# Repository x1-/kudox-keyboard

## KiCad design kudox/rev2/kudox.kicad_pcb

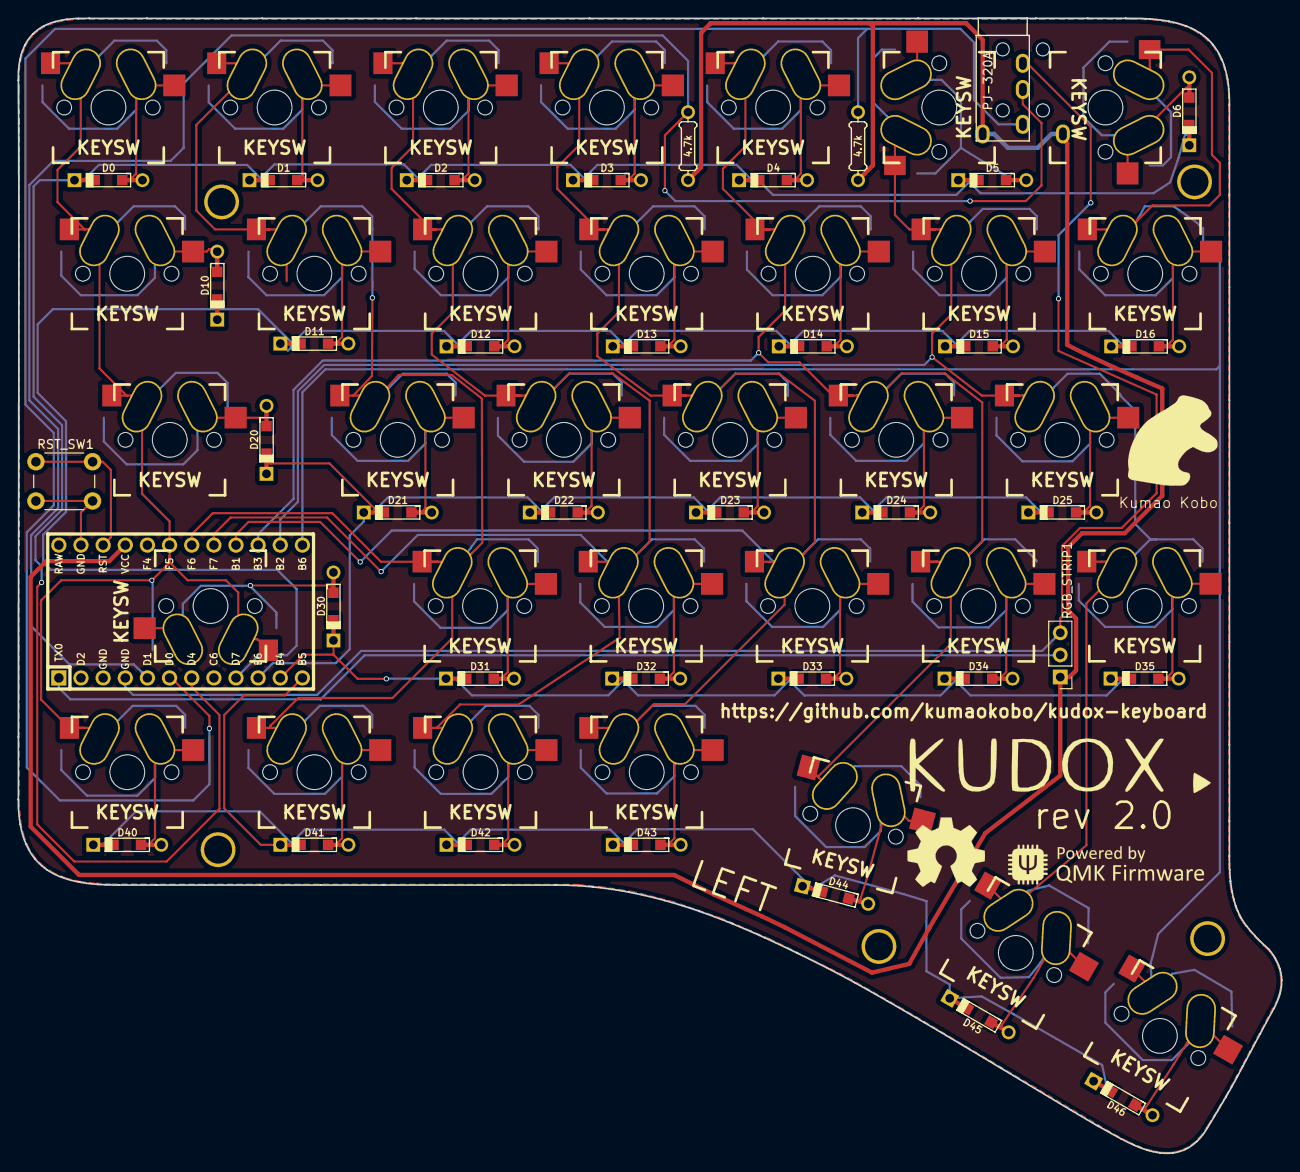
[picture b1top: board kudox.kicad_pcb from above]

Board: 2 copper layers, 144.9 x 130.2 mm, 78 parts (0 on the bottom side), 51 nets.

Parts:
-3: OSHW-Logo2_14.6x12mm_SilkScreen; OSHW-Symbol_8.9x8mm_SilkScreen
D0, D1, D2, D3, D4, D5, D6, D10, D11, D12, D13, D14, D15, D16, D20, D21, D22, D23, D24, D25, D30, D31, D32, D33, D34, D35, D40, D41, D42, D43, D44, D45, D46: D; Diode-dual
HOLE_M3, HOLE_M3#2, HOLE_M3#3, HOLE_M3#4, HOLE_M3#5: VAL**; HOLE_M3
K0, K1, K2, K3, K4, K5, K6, K10, K11, K12, K13, K14, K15, K16, K20, K21, K22, K23, K24, K25, K30, K31, K32, K33, K34, K35, K40, K41, K42, K43, K44, K45, K46: KEYSW; Mx_hotswappable
R1, R2: 4.7k; Resistor-Compact
RGB_STRIP1: Conn_01x03; Pin_Header_Straight_1x03_Pitch2.54mm
RST_SW1: SW_PUSH; SW_PUSH_6mm_h4.3mm
TRRS1: Audio-Jack-4; TRRS-PJ-320A-dual
U1: ProMicro; ArduinoProMicro

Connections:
GND: RGB_STRIP1.3, RST_SW1.2, TRRS1.4, U1.3, U1.4, U1.23
unnamed: D0.2, K0.2
unnamed: D1.2, K1.2
unnamed: D2.2, K2.2
unnamed: D3.2, K3.2
unnamed: D4.2, K4.2
unnamed: D5.2, K5.2
unnamed: D6.2, K6.2
unnamed: D10.2, K10.2
unnamed: D11.2, K11.2
unnamed: D12.2, K12.2
unnamed: D13.2, K13.2
unnamed: D14.2, K14.2
unnamed: D15.2, K15.2
unnamed: D16.2, K16.2
unnamed: D20.2, K20.2
unnamed: D21.2, K21.2
unnamed: D22.2, K22.2
unnamed: D23.2, K23.2
unnamed: D24.2, K24.2
unnamed: D25.2, K25.2
unnamed: D30.2, K30.2
unnamed: D31.2, K31.2
unnamed: D32.2, K32.2
unnamed: D33.2, K33.2
unnamed: D34.2, K34.2
unnamed: D35.2, K35.2
unnamed: D40.2, K40.2
unnamed: D41.2, K41.2
unnamed: D42.2, K42.2
unnamed: D43.2, K43.2
unnamed: D44.2, K44.2
unnamed: D45.2, K45.2
unnamed: D46.2, K46.2
RST: RST_SW1.1, U1.22
SCL: R2.1, TRRS1.2, U1.6
SDA: R1.1, TRRS1.3, U1.5
VCC: R1.2, R2.2, RGB_STRIP1.1, TRRS1.1, U1.21
col0: K0.1, K10.1, K20.1, K30.1, K40.1, U1.19
col1: K1.1, K11.1, K21.1, K31.1, K41.1, U1.18
col2: K2.1, K12.1, K22.1, K32.1, K42.1, U1.17
col3: K3.1, K13.1, K23.1, K33.1, K43.1, U1.16
col4: K4.1, K14.1, K24.1, K34.1, K44.1, U1.15
col5: K5.1, K15.1, K25.1, K35.1, K45.1, U1.14
col6: K6.1, K16.1, K46.1, U1.13
rgb_data: RGB_STRIP1.2, U1.1
row0: D0.1, D1.1, D2.1, D3.1, D4.1, D5.1, D6.1, U1.7
row1: D10.1, D11.1, D12.1, D13.1, D14.1, D15.1, D16.1, U1.9
row2: D20.1, D21.1, D22.1, D23.1, D24.1, D25.1, U1.10
row3: D30.1, D31.1, D32.1, D33.1, D34.1, D35.1, U1.11
row4: D40.1, D41.1, D42.1, D43.1, D44.1, D45.1, D46.1, U1.12

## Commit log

2019-08-02 Modified case SVGs of Kudox and Kudox Game.
2019-08-19 Add keyswitch footprint adopt Kailh hotswap socket.
2019-08-26 Add symbol libraries.
2019-08-28 Add trial PCBs,
2019-08-28 Add filled zones.
2019-08-29 Modified kudox-xs and new-pcb.
2019-08-29 Modified trivial.
2019-08-29 Modified fp-lib-table.
2019-09-30 Add kudox rev2 base components.
2019-09-30 Add a key switch on row0 col6.
2019-09-30 Add more tracks.
2019-10-04 Modified Mx hotswappable foot print.
2019-10-04 Commit on half way.
2019-10-05 Modified Pro Micro direction.
2019-10-06 Modified comments on schematic.
2019-10-06 Modified positions of holes.
2019-10-07 Modified drill aux.
2019-10-07 Modified the direction of switches on 6th row.
2019-10-09 Add icons.
2019-10-28 Modified position of ProMicro.
2019-10-31 Flip K30.
